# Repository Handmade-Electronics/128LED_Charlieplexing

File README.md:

# 128LED_Charliplexing
Arduino compatible PCB with built-in 8x16 LED screen for Charlieplexing

This is an on-going project.
The code here will be the Arduino code controlling the LEDs.
I will also include the Kicad design files for anyone who wishes to make their own boards.

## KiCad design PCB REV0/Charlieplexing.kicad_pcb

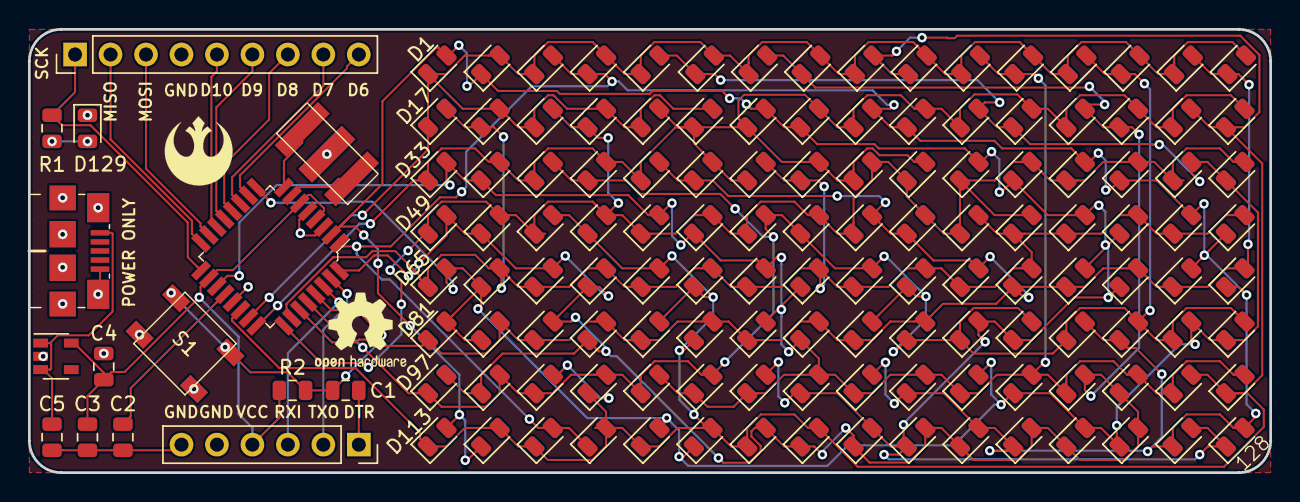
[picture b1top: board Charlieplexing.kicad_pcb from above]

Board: 2 copper layers, 88.9 x 31.8 mm, 144 parts (1 on the bottom side), 31 nets.

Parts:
128: LED_Small; LED_0805_2012Metric
C1, C2, C4: 0.1uF; C_0805_2012Metric
C3, C5: 10uF; C_0805_2012Metric
D1, D2, D3, D4, D5, D6, D7, D8, D9, D10, D11, D12, D13, D14, D15, D16, D17, D18, D19, D20, D21, D22, D23, D24, D25, D26, D27, D28, D29, D30, D31, D32, D33, D34, D35, D36, D37, D38, D39, D40, D41, D42, D43, D44, D45, D46, D47, D48, D49, D50, D51, D52, D53, D54, D55, D56, D57, D58, D59, D60, D61, D62, D63, D64, D65, D66, D67, D68, D69, D70, D71, D72, D73, D74, D75, D76, D77, D78, D79, D80, D81, D82, D83, D84, D85, D86, D87, D88, D89, D90, D91, D92, D93, D94, D95, D96, D97, D98, D99, D100, D101, D102, D103, D104, D105, D106, D107, D108, D109, D110, D111, D112, D113, D114, D115, D116, D117, D118, D119, D120, D121, D122, D123, D124, D125, D126, D127, D129: LED_Small; LED_0805_2012Metric
J1: Conn_01x06_Female; PinSocket_1x06_P2.54mm_Vertical
J2: Conn_01x09_Male; PinHeader_1x09_P2.54mm_Vertical
J4: 10118192-0001LF; USB_Micro_B_Female_10118192
R1: 330; R_0805_2012Metric
R2: 10K; R_0805_2012Metric
S1: GPTS203211B; SWITCH_PUSHBUTTON_K2-1187SQ
TWITTER: @maker_joshua; maker_joshua
U1: MIC5205-3.3YM5; SOT-23-5
U2: ATMEGA328P-AU; TQFP-32_7x7mm
Y1: Resonator_Small; RESONATOR__CSTNE_G_8MHZ

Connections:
A0: D1.1, D2.2, D3.1, D4.2, D5.1, D6.2, D7.1, D8.2, D9.1, D10.2, D11.1, D12.2, D13.1, D14.2, D15.1, D16.2, D17.1, D18.2, D19.1, D20.2, D21.1, D22.2, U2.23
A1: D21.2, D22.1, D23.1, D24.2, D25.1, D26.2, D27.1, D28.2, D29.1, D30.2, D31.1, D32.2, D33.1, D34.2, D35.1, D36.2, D37.1, D38.2, D39.1, D40.2, D41.1, D42.2, U2.24
A2: D19.2, D20.1, D41.2, D42.1, D43.1, D44.2, D45.1, D46.2, D47.1, D48.2, D49.1, D50.2, D51.1, D52.2, D53.1, D54.2, D55.1, D56.2, D57.1, D58.2, D59.1, D60.2, U2.25
A3: D17.2, D18.1, D39.2, D40.1, D59.2, D60.1, D61.1, D62.2, D63.1, D64.2, D65.1, D66.2, D67.1, D68.2, D69.1, D70.2, D71.1, D72.2, D73.1, D74.2, D75.1, D76.2, U2.26
A4: D15.2, D16.1, D37.2, D38.1, D57.2, D58.1, D75.2, D76.1, D77.1, D78.2, D79.1, D80.2, D81.1, D82.2, D83.1, D84.2, D85.1, D86.2, D87.1, D88.2, D89.1, D90.2, U2.27
A5: D13.2, D14.1, D35.2, D36.1, D55.2, D56.1, D73.2, D74.1, D89.2, D90.1, D91.1, D92.2, D93.1, D94.2, D95.1, D96.2, D97.1, D98.2, D99.1, D100.2, D101.1, D102.2, U2.28
A6: D11.2, D12.1, D33.2, D34.1, D53.2, D54.1, D71.2, D72.1, D87.2, D88.1, D101.2, D102.1, D103.1, D104.2, D105.1, D106.2, D107.1, D108.2, D109.1, D110.2, D111.1, D112.2, U2.19
A7: D9.2, D10.1, D31.2, D32.1, D51.2, D52.1, D69.2, D70.1, D85.2, D86.1, D99.2, D100.1, D111.2, D112.1, D113.1, D114.2, D115.1, D116.2, D117.1, D118.2, D119.1, D120.2, U2.22
D2: D7.2, D8.1, D29.2, D30.1, D49.2, D50.1, D67.2, D68.1, D83.2, D84.1, D97.2, D98.1, D109.2, D110.1, D119.2, D120.1, D121.1, D122.2, D123.1, D124.2, D125.1, D126.2, U2.32
D3: 128.2, D3.2, D4.1, D25.2, D26.1, D45.2, D46.1, D63.2, D64.1, D79.2, D80.1, D93.2, D94.1, D105.2, D106.1, D115.2, D116.1, D123.2, D124.1, D127.1, U2.1
D4: 128.1, D1.2, D2.1, D23.2, D24.1, D43.2, D44.1, D61.2, D62.1, D77.2, D78.1, D91.2, D92.1, D103.2, D104.1, D113.2, D114.1, D121.2, D122.1, D127.2, U2.2
D5: D5.2, D6.1, D27.2, D28.1, D47.2, D48.1, D65.2, D66.1, D81.2, D82.1, D95.2, D96.1, D107.2, D108.1, D117.2, D118.1, D125.2, D126.1, U2.9
D6: J2.9, U2.10
D7: J2.8, U2.11
D8: J2.7, U2.12
D9: J2.6, U2.13
D10: J2.5, U2.14
DTR: C1.1, J1.1
GND: C2.1, C3.2, C4.2, C5.2, D129.1, J1.5, J1.6, J2.4, J4.5, J4.SH, S1.2, U1.2, U2.3, U2.5, U2.21, Y1.2
MISO: J2.2, U2.16
MOSI: J2.3, U2.15
unnamed: C1.2, R2.2, S1.1, U2.29
unnamed: C2.2, U2.20
unnamed: C5.1, J4.1, U1.1, U1.3
unnamed: D129.2, R1.1
unnamed: U2.7, Y1.1
unnamed: U2.8, Y1.3
RXI: J1.3, U2.30
SCK: J2.1, R1.2, U2.17
TXO: J1.2, U2.31
VCC: C3.1, C4.1, J1.4, R2.1, U1.5, U2.4, U2.6, U2.18

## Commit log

2018-12-03 Add files via upload
    Revision 1 of the board design. Pin design using ADC6 and ADC7 have been replaced with data files, and all data pins were re-arranged.
2018-12-03 Set theme jekyll-theme-midnight

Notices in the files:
PCB REV0/Charlieplexing.kicad_pcb:
RELEASED UNDER THE CREATIVE COMMONS ATTRIBUTION SHARE-ALIKE 3.0 LICENSE
